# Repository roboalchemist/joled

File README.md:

# MicroPython OLED Controller Library

A MicroPython library for controlling I2C OLED displays with integrated button input support. Features a compact 5x7 bitmap font for clear text rendering on small displays.

## Features

- **I2C OLED Display Support**: Compatible with SSD1306 and similar OLED controllers
- **Button Input**: I2C GPIO expander support for multiple buttons
- **5x7 Bitmap Font**: Includes comprehensive character set with special symbols
- **Graphics Primitives**: Lines, rectangles, pixels, and text rendering
- **Easy Installation**: Install via `mpremote mip install`

## Installation

### Using mpremote (Recommended)

```bash
mpremote mip install github:roboalchemist/joled
```

### Manual Installation

1. Download the library files
2. Copy the `oled_controller` folder to your MicroPython device's lib directory

## Quick Start

```python
from oled_controller import OLEDController

# Initialize JOLED controller with RGB support
controller = OLEDController.create()

# Clear display and show text
controller.clear()
controller.text("Hello World!", 0, 0)
controller.center_text("Centered", 20)
controller.rgb_color('blue')  # Set LED to blue
controller.show()

# Check button input (8 total inputs: 5-way D-pad + 3 buttons)
controller.update_buttons()
if controller.button_just_pressed(7):  # Center button
    controller.clear()
    controller.text("Center pressed!", 0, 0)
    controller.rgb_color('green')  # Change LED to green
    controller.show()
```

## Hardware Setup

### JOLED Controller Specifications

The JOLED controller follows the QWIIC standard (https://www.sparkfun.com/qwiic) for easy connectivity.

**I2C Configuration:**
- **SCL**: Pin 7
- **SDA**: Pin 6  
- **Frequency**: 400kHz

**Components:**

#### 128x64 SSD1306 OLED Display
- **I2C Address**: 0x3C (default)
- **Resolution**: 128x64 pixels
- Connected via I2C bus

#### PCF8575 Port Expander  
- **I2C Address**: 0x20
- **Initialization**: Write 0x0007 to establish baseline state (buttons low, LEDs high/off)

**Controls:**

#### 5-Way D-Pad (Active High, Pulled Low)
- **Up**: P6
- **Down**: P4  
- **Left**: P5
- **Right**: P3
- **Center**: P7

#### 3 Buttons (Active High, Pulled Low)
- **B1**: P2
- **B2**: P1
- **B3**: P0

#### RGB LED (Active Low)
- **Red**: P8
- **Green**: P9
- **Blue**: P10

**Physical Layout:**
```
JOLED Controller:
        ------------------------------------------
        |                              [RGB]     |
[qwiic]<|    ----------------        U           |>[qwiic]
        |    |    128x64    |     L  C  R        |
        |    | SSD1306 OLED |        D           |
[qwiic]<|    ----------------                    |>[qwiic]
        |                       B1   B2  B3      |
        ------------------------------------------
```

### Generic I2C Setup (Other Hardware)
- **SDA**: Connect to your microcontroller's SDA pin (default: GPIO 4)
- **SCL**: Connect to your microcontroller's SCL pin (default: GPIO 5)  
- **VCC**: 3.3V or 5V (depending on display)
- **GND**: Ground

## API Reference

### OLEDController Class

#### Initialization
```python
# JOLED Controller (recommended)
controller = OLEDController.create()  # Pre-configured for JOLED

# Or manually configure JOLED
controller = OLEDController(
    sda_pin=6,          # JOLED SDA pin
    scl_pin=7,          # JOLED SCL pin
    num_buttons=8,      # 5-way D-pad + 3 buttons
    has_rgb=True        # Enable RGB LED support
)

# Generic setup (other hardware)
controller = OLEDController(
    i2c_bus=0,          # I2C bus number (0 or 1)
    sda_pin=4,          # SDA pin number
    scl_pin=5,          # SCL pin number
    oled_addr=0x3C,     # OLED I2C address
    button_addr=0x20,   # Button controller I2C address
    width=128,          # Display width in pixels
    height=64,          # Display height in pixels
    num_buttons=4       # Number of buttons
)
```

#### Display Methods
```python
# Method 1: Direct controller methods
controller.clear()                    # Clear display
controller.show()                     # Update display
controller.pixel(x, y, color=1)      # Set pixel
controller.line(x0, y0, x1, y1, color=1)  # Draw line
controller.rect(x, y, w, h, color=1)      # Draw rectangle
controller.fill_rect(x, y, w, h, color=1) # Draw filled rectangle
controller.text(text, x, y, color=1)      # Draw text
controller.center_text(text, y, color=1)  # Draw centered text
controller.text_width(text)               # Get text width
controller.contrast(level)                # Set contrast (0-255)
controller.invert(True/False)             # Invert colors
controller.poweroff()                     # Turn off display

# Method 2: Display sub-controller access (recommended)
controller.disp.clear()                  # Direct display control
controller.disp.show()                   # Update display
controller.disp.pixel(x, y, color)       # Set pixel
controller.disp.text(text, x, y)         # Draw text
controller.disp.center_text(text, y)     # Centered text
```

#### Button Methods
```python
# Method 1: Direct controller methods
controller.update_buttons()           # Update button states
controller.button_pressed(button)     # Check if button is pressed
controller.button_just_pressed(button) # Check if button was just pressed
controller.get_pressed_buttons()      # Get list of pressed buttons
controller.get_just_pressed_buttons() # Get list of just pressed buttons

# Method 2: Button sub-controller access (recommended)
controller.btns.update()          # Update button states
controller.btns.is_pressed(button) # Check if button is pressed
controller.btns.was_pressed(button) # Check if button was just pressed
controller.btns.get_pressed_buttons() # Get list of pressed buttons
controller.btns.get_just_pressed_buttons() # Get list of just pressed
```

#### RGB LED Methods (JOLED Only)
```python
# Method 1: Direct controller methods
controller.set_rgb(red=True, green=False, blue=False)  # Set individual colors
controller.rgb_color('red')                           # Set predefined color
controller.rgb_off()                                  # Turn off RGB LED

# Method 2: RGB sub-controller access (recommended)
controller.rgb.set(red=True, green=False, blue=False) # Direct RGB control
controller.rgb.color('red')                           # Set predefined color
controller.rgb.off()                                  # Turn off RGB LED

# Animations (both methods work)
controller.rgb_pulse('blue', speed=0.1, count=5, callback=func)  # Via controller
controller.rgb.pulse('blue', speed=0.1, count=5, callback=func)  # Via sub-controller

controller.rgb_flash('red', count=3, on_time=200, off_time=200)  # Via controller  
controller.rgb.flash('red', count=3, on_time=200, off_time=200)  # Via sub-controller

# Animation control
controller.rgb_stop_animation()  # or controller.rgb.stop_animation()
controller.rgb_is_animating()    # or controller.rgb.is_animating()
```

#### Utility Methods
```python
controller.scan_i2c()               # Scan I2C bus for devices

# JOLED Helper
controller = OLEDController.create()  # Pre-configured for JOLED
```

### Standalone Sub-Controllers

```python
from oled_controller import DisplayController, ButtonController, RGBController
from machine import I2C, Pin

# Create I2C bus
i2c = I2C(0, sda=Pin(6), scl=Pin(7))

# Create standalone controllers
disp = DisplayController(i2c, width=128, height=64, addr=0x3C)
btns = ButtonController(i2c, addr=0x20, num_buttons=8, is_joled=True)  
rgb = RGBController(i2c, addr=0x20)

# Use independently
disp.clear()
disp.text("Standalone", 0, 0)
disp.show()

btns.update()
if btns.is_pressed(0):
    rgb.color('red')
```

### Font5x7 Class

```python
from oled_controller import Font5x7

font = Font5x7()
char_data = font.get_char_data('A')   # Get bitmap data for character
width = font.text_width("Hello")      # Calculate text width
exists = font.char_exists('€')        # Check if character exists
```

## Supported Characters

The 5x7 font includes:
- **ASCII**: Letters (A-Z, a-z), numbers (0-9), punctuation
- **Special**: German umlauts (Ä, Ö, Ü, ä, ö, ü)
- **Symbols**: Euro (€), degree (°), arrows (→, ←)

## Examples

### Basic Display
```python
from oled_controller import OLEDController

controller = OLEDController()
controller.clear()
controller.text("MicroPython", 0, 0)
controller.text("OLED Library", 0, 10)
controller.rect(0, 20, 128, 20)
controller.show()
```

### JOLED Button Input
```python
from oled_controller import OLEDController
import time

controller = OLEDController(sda_pin=6, scl_pin=7, num_buttons=8)

# Button mapping for JOLED
button_names = ["B3", "B2", "B1", "Right", "Down", "Left", "Up", "Center"]

while True:
    controller.update_buttons()
    
    controller.clear()
    controller.text("JOLED Controls:", 0, 0)
    
    for i in range(8):
        if controller.button_pressed(i):
            controller.text(f"{button_names[i]}: ON", 0, 10 + (i%6)*8)
        else:
            controller.text(f"{button_names[i]}: OFF", 70, 10 + (i%6)*8)
    
    controller.show()
    time.sleep(0.1)
```

### JOLED RGB LED Demo
```python
from oled_controller import OLEDController
import time

# Initialize JOLED with RGB support
controller = OLEDController.create()

colors = ['red', 'green', 'blue', 'yellow', 'magenta', 'cyan', 'white']

for color in colors:
    controller.clear()
    controller.center_text(f"Color: {color}", 20)
    controller.rgb_color(color)
    controller.show()
    time.sleep(1)

controller.rgb_off()
```

### All Sub-Controllers Demo
```python
from oled_controller import OLEDController
import time

controller = OLEDController.create()

# Access all sub-controllers
disp = controller.disp
btns = controller.btns
rgb = controller.rgb

# Display sub-controller
disp.clear()
disp.center_text("Sub-Controllers", 10)
disp.center_text("Demo", 25)
disp.show()

# RGB sub-controller
rgb.color('blue')
time.sleep(1)

# Button sub-controller
while True:
    btns.update()
    pressed = btns.get_pressed_buttons()
    
    if pressed:
        disp.clear()
        disp.text(f"Pressed: {pressed}", 0, 20)
        disp.show()
        
        # Change RGB based on buttons
        if 0 in pressed:
            rgb.color('red')
        elif 1 in pressed:
            rgb.pulse('green', count=2)
            
    if btns.was_pressed(7):  # Center to exit
        break
    
    time.sleep(0.05)

rgb.off()
```

### Graphics Demo
```python
from oled_controller import OLEDController

controller = OLEDController()
controller.clear()

# Draw some graphics
controller.line(0, 0, 127, 63)
controller.rect(10, 10, 20, 20)
controller.fill_rect(50, 20, 30, 15)
controller.center_text("Graphics!", 50)

controller.show()
```

## Configuration

### JOLED Controller Setup
```python
# JOLED with RGB LED support
controller = OLEDController.create()
# Or: controller = OLEDController(sda_pin=6, scl_pin=7, num_buttons=8, has_rgb=True)
```

### Custom I2C Pins (Other Hardware)
```python
# Use different I2C pins for generic hardware
controller = OLEDController(sda_pin=21, scl_pin=22)
```

### Different Display Size
```python
# 128x32 display
controller = OLEDController(width=128, height=32)
```

### Existing I2C Bus
```python
from machine import I2C, Pin

# Use existing I2C instance
i2c = I2C(0, sda=Pin(4), scl=Pin(5))
controller = OLEDController(i2c_bus=i2c)
```

## Troubleshooting

### Display Not Working
1. Check I2C connections (SDA, SCL, VCC, GND)
2. Verify I2C address: `controller.scan_i2c()`
3. Try different contrast: `controller.contrast(255)`
4. Check power supply voltage

### Button Input Not Working
1. Verify button controller I2C address
2. Check GPIO expander connections
3. The library will work without buttons if no GPIO expander is found

### JOLED Button Mapping
```python
# JOLED button mapping (PCF8575 pins P0-P7)
BUTTON_MAP = {
    0: "B3",     # P0 - Button 3
    1: "B2",     # P1 - Button 2  
    2: "B1",     # P2 - Button 1
    3: "Right",  # P3 - D-pad Right
    4: "Down",   # P4 - D-pad Down
    5: "Left",   # P5 - D-pad Left
    6: "Up",     # P6 - D-pad Up
    7: "Center"  # P7 - D-pad Center
}
```

### JOLED RGB LED Control
```python
# Initialize JOLED with RGB support
controller = OLEDController.create()

# Set individual colors
controller.set_rgb(red=True, green=False, blue=False)  # Red only
controller.set_rgb(red=True, green=True, blue=False)   # Yellow

# Use predefined colors
controller.rgb_color('red')      # Red
controller.rgb_color('green')    # Green  
controller.rgb_color('blue')     # Blue
controller.rgb_color('yellow')   # Yellow
controller.rgb_color('magenta')  # Magenta
controller.rgb_color('cyan')     # Cyan
controller.rgb_color('white')    # White
controller.rgb_color('off')      # Turn off

# Turn off RGB LED
controller.rgb_off()

# Pulsing animation
def pulse_done():
    print("Pulsing completed!")

controller.rgb_pulse('red', speed=0.1, pulses=3, callback=pulse_done)

# Flashing animation  
controller.rgb_flash('blue', count=5, on_time=200, off_time=100)

# Stop any animation
controller.rgb_stop_animation()
```

### Common I2C Addresses
- **OLED Display**: 0x3C or 0x3D
- **JOLED PCF8575**: 0x20
- **GPIO Expanders**: 0x20-0x27 (MCP23017), 0x38-0x3F (PCF8574)

## Hardware Compatibility

### Tested Microcontrollers
- ESP32
- ESP8266
- Raspberry Pi Pico (RP2040)

### Tested OLED Displays
- 128x64 SSD1306
- 128x32 SSD1306

### JOLED Hardware
- PCF8575 (16-bit I2C GPIO expander)
- 128x64 SSD1306 OLED display
- 5-way D-pad navigation
- 3 additional buttons
- RGB LED indicator

### Generic GPIO Expanders  
- MCP23017 (16-bit)
- PCF8574 (8-bit)
- Generic I2C GPIO expanders

## License

MIT License - see LICENSE file for details.

## Contributing

Contributions welcome! Please submit issues and pull requests on GitHub.

## Version History

- **1.0.0**: Initial release with OLED and button support

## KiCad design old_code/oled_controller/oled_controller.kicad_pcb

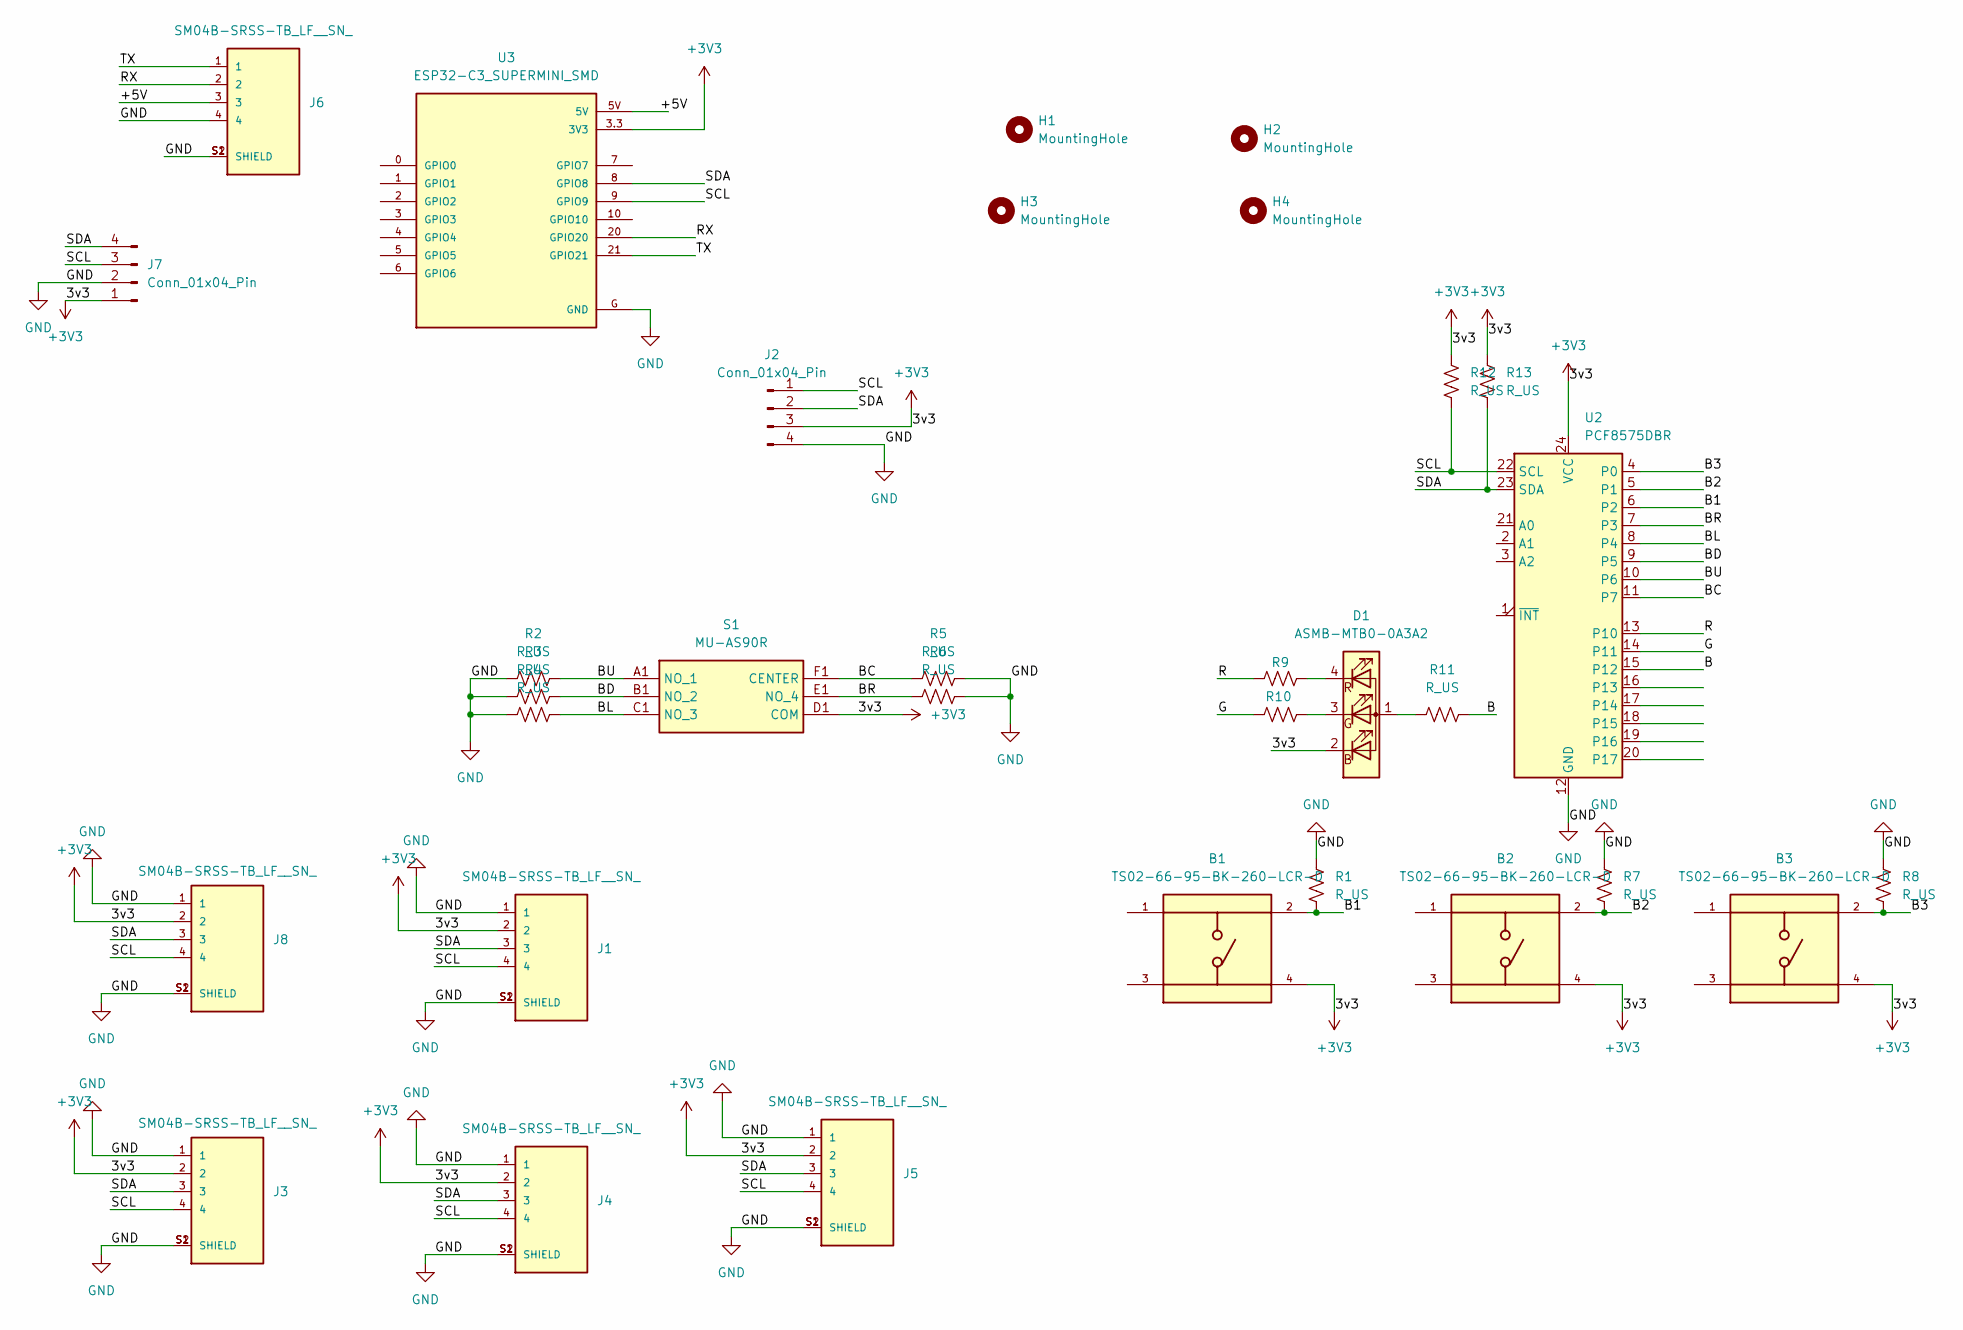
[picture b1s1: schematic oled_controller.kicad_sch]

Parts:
B1, B2, B3: TS02-66-95-BK-260-LCR-D; SW_TS02-66-95-BK-260-LCR-D; PARTREV 1.0
D1: ASMB-MTB0-0A3A2; LED_Avago_PLCC4_3.2x2.8mm_CW
H1, H2, H3, H4: MountingHole; MountingHole_3.2mm_M3
J1, J3, J4, J5, J6, J8: SM04B-SRSS-TB_LF__SN_; JST_SM04B-SRSS-TB_LF__SN_
J2: Conn_01x04_Pin; JST_XH_B4B-XH-A_1x04_P2.50mm_Vertical
J7: Conn_01x04_Pin; PinSocket_1x04_P2.54mm_Vertical
R1, R2, R3, R4, R5, R6, R7, R8, R9, R10, R11, R12, R13: R_US; R_0805_2012Metric_Pad1.20x1.40mm_HandSolder
S1: MU-AS90R; MUAS90R; Mouser Part Number 642-MU-AS90R
U2: PCF8575DBR; SSOP-24_5.3x8.2mm_P0.65mm
U3: ESP32-C3_SUPERMINI_SMD; MODULE_ESP32-C3_SUPERMINI

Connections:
+3V3: B1.4, B2.4, B3.4, D1.2 (BK), J1.2, J2.3, J3.2, J4.2, J5.2, J7.1, J8.2, R12.1, R13.1, S1.D1 (COM), U2.24 (VCC), U3.3.3 (3V3)
/+5V: J6.3, U3.5V
/B: R11.2, U2.15 (P12)
/B1: B1.2, R1.1, U2.6 (P2)
/B2: B2.2, R7.2, U2.5 (P1)
/B3: B3.2, R8.1, U2.4 (P0)
/BC: R5.1, S1.F1 (CENTER), U2.11 (P7)
/BD: R3.2, S1.B1 (NO_2), U2.9 (P5)
/BL: R4.2, S1.C1 (NO_3), U2.8 (P4)
/BR: R6.1, S1.E1 (NO_4), U2.7 (P3)
/BU: R2.2, S1.A1 (NO_1), U2.10 (P6)
/G: R10.2, U2.14 (P11)
/R: R9.2, U2.13 (P10)
/RX: J6.2, U3.20 (GPIO20)
/SCL: J1.4, J2.1, J3.4, J4.4, J5.4, J7.3, J8.4, R12.2, U2.22 (SCL), U3.9 (GPIO9)
/SDA: J1.3, J2.2, J3.3, J4.3, J5.3, J7.4, J8.3, R13.2, U2.23 (SDA), U3.8 (GPIO8)
/TX: J6.1, U3.21 (GPIO21)
GND: J1.1, J1.S1 (SHIELD), J1.S2 (SHIELD), J2.4, J3.1, J3.S1 (SHIELD), J3.S2 (SHIELD), J4.1, J4.S1 (SHIELD), J4.S2 (SHIELD), J5.1, J5.S1 (SHIELD), J5.S2 (SHIELD), J6.4, J6.S1 (SHIELD), J6.S2 (SHIELD), J7.2, J8.1, J8.S1 (SHIELD), J8.S2 (SHIELD), R1.2, R2.1, R3.1, R4.1, R5.2, R6.2, R7.1, R8.2, U2.12 (GND), U3.G (GND)
unnamed: D1.1 (A), R11.1
unnamed: D1.3 (GK), R10.1
unnamed: D1.4 (RK), R9.1

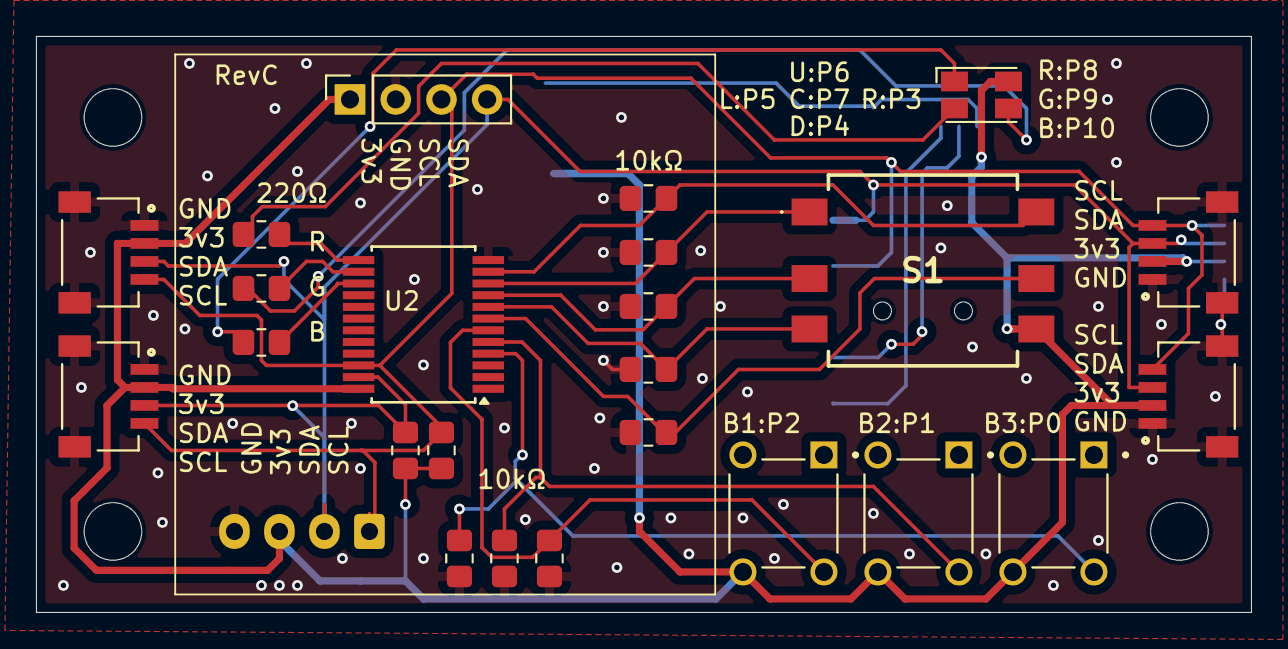
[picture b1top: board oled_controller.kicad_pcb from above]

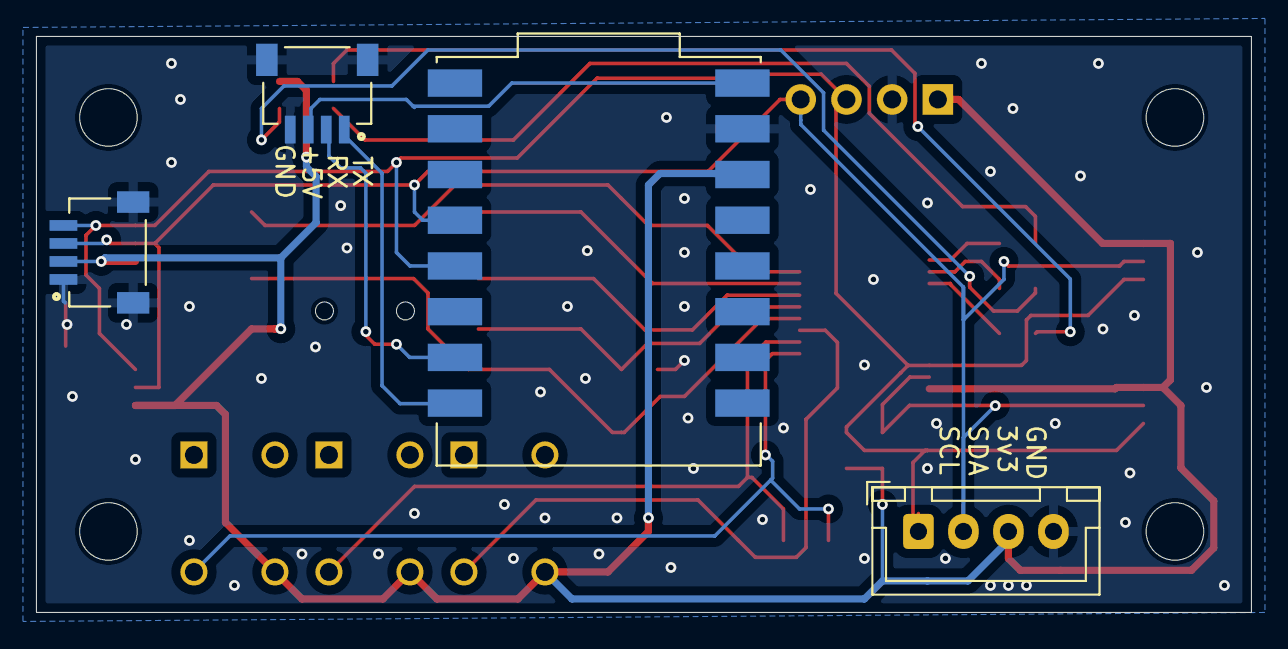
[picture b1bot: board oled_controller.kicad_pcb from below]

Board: 2 copper layers, 67.5 x 32.0 mm, 32 parts (4 on the bottom side), 21 nets.

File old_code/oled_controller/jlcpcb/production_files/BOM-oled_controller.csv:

Comment,Designator,Footprint,LCSC
MU-AS90R,S1,MUAS90R,
R_US,R10,R_0805_2012Metric_Pad1.20x1.40mm_HandSolder,
R_US,R9,R_0805_2012Metric_Pad1.20x1.40mm_HandSolder,
R_US,R8,R_0805_2012Metric_Pad1.20x1.40mm_HandSolder,
R_US,R7,R_0805_2012Metric_Pad1.20x1.40mm_HandSolder,
ASMB-MTB0-0A3A2,D1,LED_Avago_PLCC4_3.2x2.8mm_CW,
PCF8575DBR,U2,SSOP-24_5.3x8.2mm_P0.65mm,
SM04B-SRSS-TB_LF__SN_,J8,JST_SM04B-SRSS-TB_LF__SN_,
SM04B-SRSS-TB_LF__SN_,J1,JST_SM04B-SRSS-TB_LF__SN_,
Conn_01x04_Pin,J7,PinSocket_1x04_P2.54mm_Vertical,
R_US,R3,R_0805_2012Metric_Pad1.20x1.40mm_HandSolder,
R_US,R4,R_0805_2012Metric_Pad1.20x1.40mm_HandSolder,
R_US,R6,R_0805_2012Metric_Pad1.20x1.40mm_HandSolder,
R_US,R2,R_0805_2012Metric_Pad1.20x1.40mm_HandSolder,
R_US,R5,R_0805_2012Metric_Pad1.20x1.40mm_HandSolder,
Conn_01x04_Pin,J2,JST_XH_B4B-XH-A_1x04_P2.50mm_Vertical,
R_US,R1,R_0805_2012Metric_Pad1.20x1.40mm_HandSolder,
R_US,R11,R_0805_2012Metric_Pad1.20x1.40mm_HandSolder,
R_US,R13,R_0805_2012Metric_Pad1.20x1.40mm_HandSolder,
R_US,R12,R_0805_2012Metric_Pad1.20x1.40mm_HandSolder,
SM04B-SRSS-TB_LF__SN_,J4,JST_SM04B-SRSS-TB_LF__SN_,
SM04B-SRSS-TB_LF__SN_,J3,JST_SM04B-SRSS-TB_LF__SN_,
TS02-66-95-BK-260-LCR-D,B2,SW_TS02-66-95-BK-260-LCR-D,
TS02-66-95-BK-260-LCR-D,B1,SW_TS02-66-95-BK-260-LCR-D,
TS02-66-95-BK-260-LCR-D,B3,SW_TS02-66-95-BK-260-LCR-D,
SM04B-SRSS-TB_LF__SN_,J5,JST_SM04B-SRSS-TB_LF__SN_,
ESP32-C3_SUPERMINI_SMD,U3,MODULE_ESP32-C3_SUPERMINI,
SM04B-SRSS-TB_LF__SN_,J6,JST_SM04B-SRSS-TB_LF__SN_,

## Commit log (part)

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2025-03-16 add existing old controller code
